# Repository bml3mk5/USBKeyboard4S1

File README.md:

# USBキーボード for 日立 MB-S1

## フォルダ構成

    Board/ ......................... 基板設計
      KiCad/ ....................... KiCad Version 6  通常基板(DIPタイプを使用)
      EasyEDA/ ..................... EasyEDA 6.5      小型基板(表面実装)
    Software/ ...................... PICマイコン用ソフトウェア

### [ラズパイPico版はこちら](https://github.com/bml3mk5/USBKeyboard4S1_PiPico)

-----
# USBKeyboard for HITACHI MB-S1

## Folders:

    Board/ ......................... Circuit board design
      KiCad/ ....................... KiCad Version 6  Normal board (using DIP type PIC micro controller)
      EasyEDA/ ..................... EasyEDA 6.5      Small board (using SMT type)
    Software/ ...................... Software for PIC micro controller

### [Raspberry Pi Pico version is here](https://github.com/bml3mk5/USBKeyboard4S1_PiPico)

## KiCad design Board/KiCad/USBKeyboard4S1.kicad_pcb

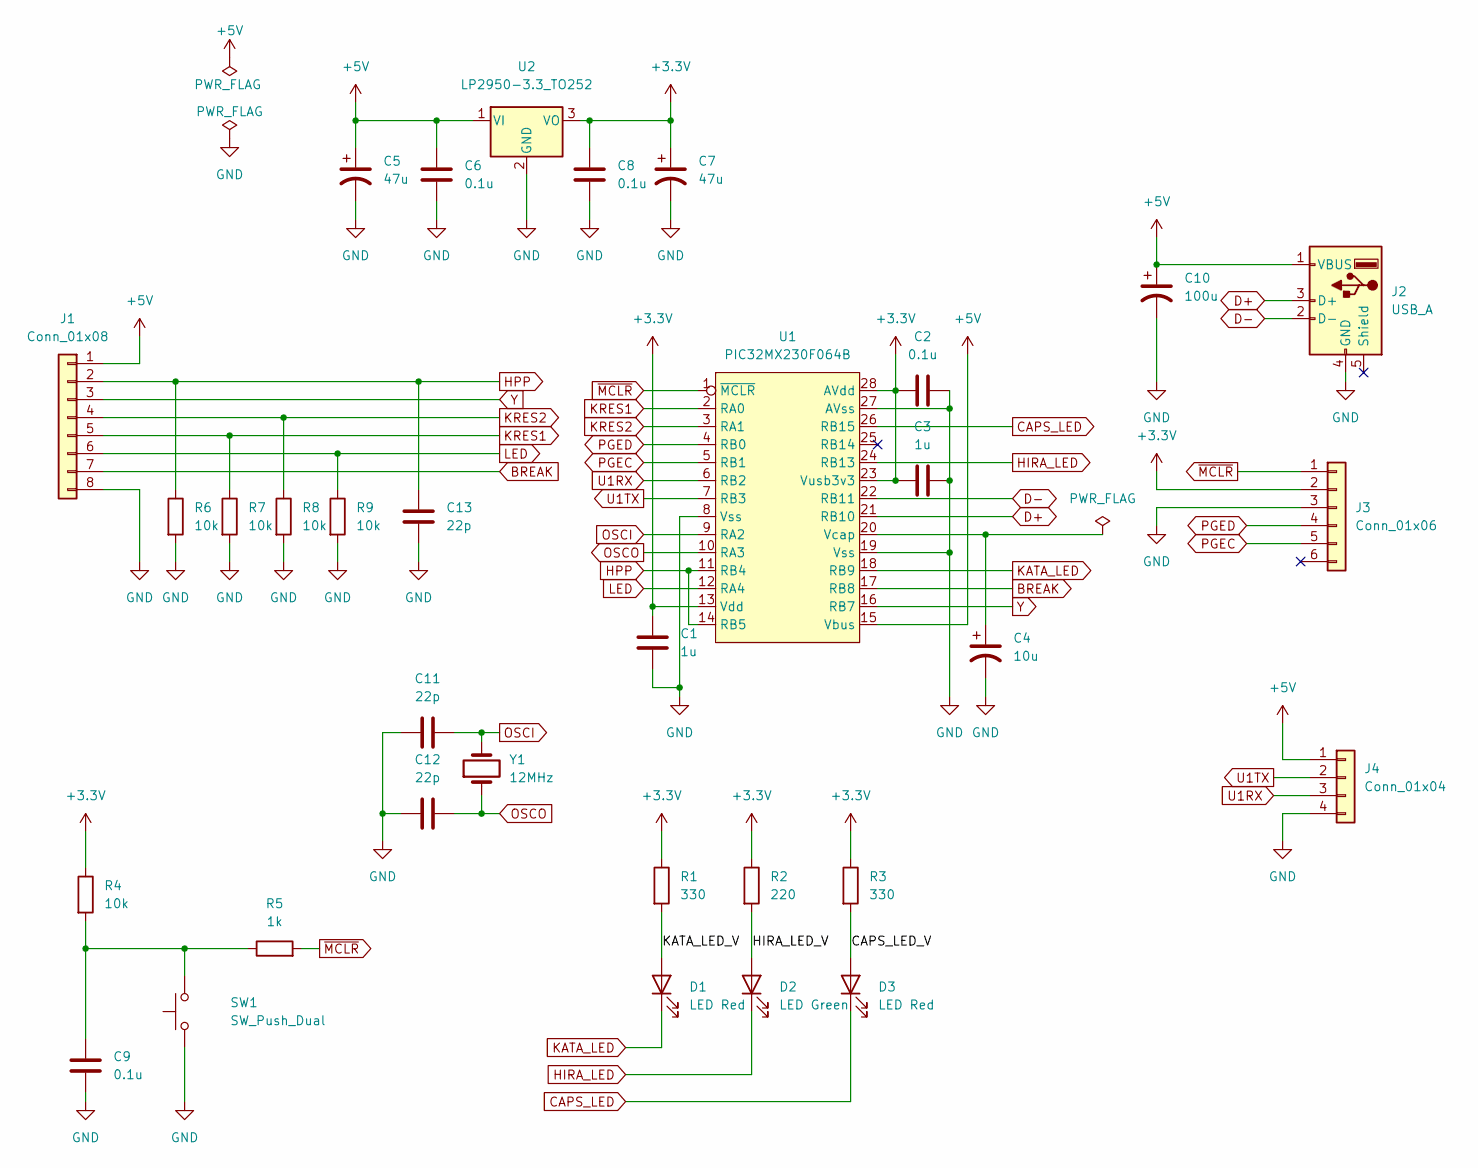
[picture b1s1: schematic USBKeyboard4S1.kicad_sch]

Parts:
C1, C3: 1u; C_Disc_D3.0mm_W2.0mm_P2.50mm
C2, C6, C8, C9: 0.1u; C_Disc_D3.0mm_W2.0mm_P2.50mm
C4: 10u; CP_Radial_D5.0mm_P2.50mm
C5, C7: 47u; CP_Radial_D5.0mm_P2.50mm
C10: 100u; CP_Radial_D6.3mm_P2.50mm
C11, C12, C13: 22p; C_Disc_D3.0mm_W2.0mm_P2.50mm
D1, D3: LED Red; LED_D2.0mm_W4.8mm_H2.5mm_FlatTop
D2: LED Green; LED_D2.0mm_W4.8mm_H2.5mm_FlatTop
J1: Conn_01x08; JST_XH_B8B-XH-A_1x08_P2.50mm_Vertical
J2: USB_A; USB_A_Horizontal
J3: Conn_01x06; PinHeader_1x06_P2.54mm_Vertical
J4: Conn_01x04; PinHeader_1x04_P2.54mm_Vertical
R1, R3: 330; R_Axial_DIN0207_L6.3mm_D2.5mm_P2.54mm_Vertical
R2: 220; R_Axial_DIN0207_L6.3mm_D2.5mm_P2.54mm_Vertical
R4, R6, R7, R8, R9: 10k; R_Axial_DIN0207_L6.3mm_D2.5mm_P2.54mm_Vertical
R5: 1k; R_Axial_DIN0207_L6.3mm_D2.5mm_P2.54mm_Vertical
SW1: SW_Push_Dual; SW_PUSH_6mm
U1: PIC32MX230F064B; DIP-28_W7.62mm_Socket
U2: LP2950-3.3_TO252; TO-262-3_Vertical
Y1: 12MHz; Crystal_HC18-U_Vertical

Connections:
+3.3V: C1.1, C2.1, C3.1, C7.1, C8.2, J3.2, R1.1, R2.1, R3.1, R4.1, U1.13 (Vdd), U1.23 (Vusb3v3), U1.28 (AVdd), U2.3 (VO)
+5V: C5.1, C6.2, C10.1, J1.1, J2.1 (VBUS), J4.1, U1.15 (Vbus), U2.1 (VI)
/CAPS_LED_V: D3.1 (A), R3.2
/HIRA_LED_V: D2.1 (A), R2.2
/KATA_LED_V: D1.1 (A), R1.2
BREAK: J1.7, U1.17 (RB8)
CAPS_LED: D3.2 (K), U1.26 (RB15)
D+: J2.3 (D+), U1.21 (RB10)
D-: J2.2 (D-), U1.22 (RB11)
GND: C1.2, C2.2, C3.2, C4.2, C5.2, C6.1, C7.2, C8.1, C9.1, C10.2, C11.1, C12.1, C13.1, J1.8, J2.4 (GND), J3.3, J4.4, R6.2, R7.2, R8.2, R9.2, SW1.1, U1.8 (Vss), U1.19 (Vss), U1.27 (AVss), U2.2 (GND)
HIRA_LED: D2.2 (K), U1.24 (RB13)
HPP: C13.2, J1.2, R6.1, U1.11 (RB4), U1.14 (RB5)
KATA_LED: D1.2 (K), U1.18 (RB9)
KRES1: J1.5, R7.1, U1.2 (RA0)
KRES2: J1.4, R8.1, U1.3 (RA1)
LED: J1.6, R9.1, U1.12 (RA4)
unnamed: C4.1, U1.20 (Vcap)
unnamed: C9.2, R4.2, R5.1, SW1.2
OSCI: C11.2, U1.9 (RA2), Y1.2
OSCO: C12.2, U1.10 (RA3), Y1.1
PGEC: J3.5, U1.5 (RB1)
PGED: J3.4, U1.4 (RB0)
U1RX: J4.3, U1.6 (RB2)
U1TX: J4.2, U1.7 (RB3)
Y: J1.3, U1.16 (RB7)
~MCLR: J3.1, R5.2, U1.1 (~MCLR)

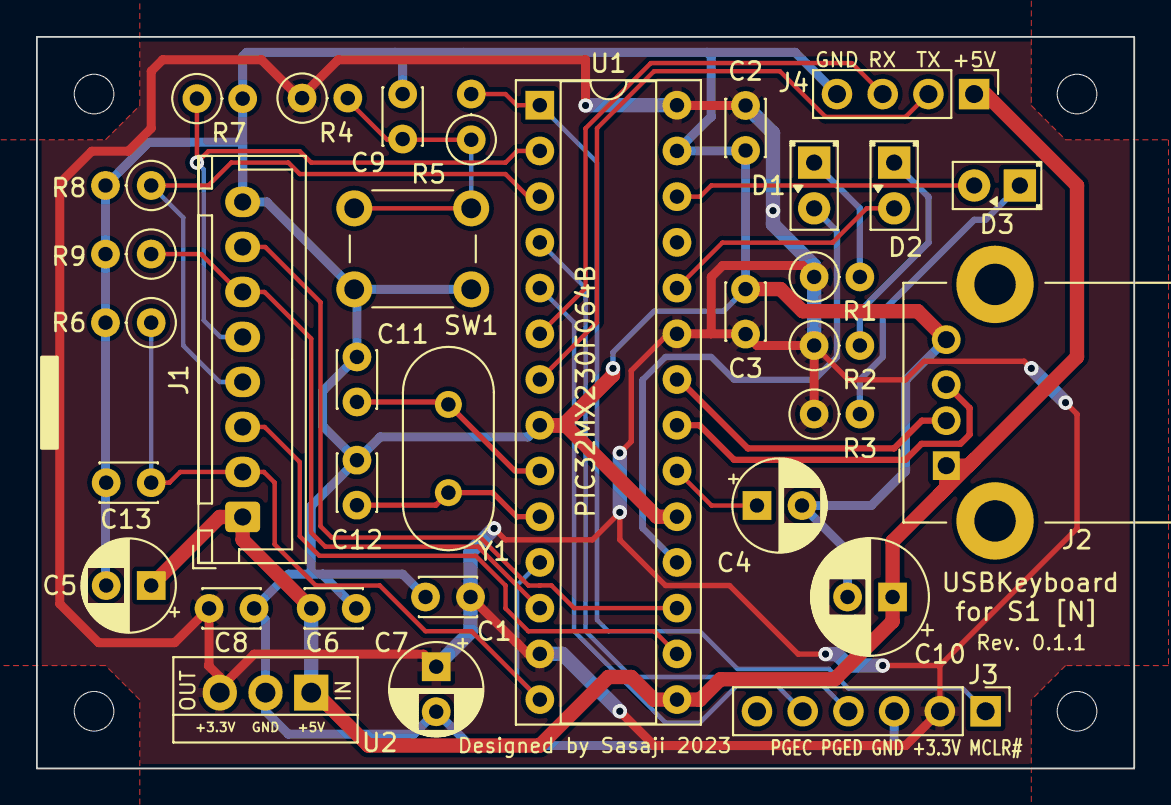
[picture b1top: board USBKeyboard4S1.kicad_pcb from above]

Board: 2 copper layers, 61.0 x 40.6 mm, 33 parts (0 on the bottom side), 26 nets.

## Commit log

2023-05-20 Initial version
2023-05-23 Modify software and documents
2023-05-26 Revision 0.1
2023-07-30 Modify documents and source codes
2023-10-21 Hardware version 0.1.1
2025-05-02 Modify documents
